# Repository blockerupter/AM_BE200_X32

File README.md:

AM_BE200_X32
============

BE200 Board with 32 chips

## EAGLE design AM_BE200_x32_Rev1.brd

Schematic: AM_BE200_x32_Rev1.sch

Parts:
C1, C17, C33, C49, C65, C81, C97, C113: 100uF; 153CLV-0605
C2, C3, C4, C5, C18, C19, C20, C21, C34, C35, C36, C37, C50, C51, C52, C53, C66, C67, C68, C69, C82, C83, C84, C85, C98, C99, C100, C101, C114, C115, C116, C117: 22uF; C1210K
C6, C7, C22, C23, C38, C39, C54, C55, C70, C71, C86, C87, C102, C103, C118, C119: 4.7uF; C0805K
C8, C24, C40, C56, C72, C88, C104, C120: 1nF; C0805K
C9, C25, C41, C57, C73, C89, C105, C121: 22nF; C0805K
C10, C26, C42, C58, C74, C90, C106, C122, C361, C362, C364, C367, C368, C369, C370, C371, C372: 100nF; C0805K
C11, C27, C43, C59, C75, C91, C107, C123, C354: 2,2nF; C0805K
C12, C13, C14, C15, C16, C28, C29, C30, C31, C32, C44, C45, C46, C47, C48, C60, C61, C62, C63, C64, C76, C77, C78, C79, C80, C92, C93, C94, C95, C96, C108, C109, C110, C111, C112, C124, C125, C126, C127, C128: 100uF; C1210K
C129, C130, C131, C132, C134, C136, C137, C138, C139, C141, C143, C144, C145, C146, C148, C150, C151, C152, C153, C155, C157, C158, C159, C160, C162, C164, C165, C166, C167, C169, C171, C172, C173, C174, C176, C178, C179, C180, C181, C183, C185, C186, C187, C188, C190, C192, C193, C194, C195, C197, C199, C200, C201, C202, C204, C206, C207, C208, C209, C211, C213, C214, C215, C216, C218, C220, C221, C222, C223, C225, C227, C228, C229, C230, C232, C234, C235, C236, C237, C239, C241, C242, C243, C244, C246, C248, C249, C250, C251, C253, C255, C256, C257, C258, C260, C262, C263, C264, C265, C267, C269, C270, C271, C272, C274, C276, C277, C278, C279, C281, C283, C284, C285, C286, C288, C290, C291, C292, C293, C295, C297, C298, C299, C300, C302, C304, C305, C306, C307, C309, C311, C312, C313, C314, C316, C318, C319, C320, C321, C323, C325, C326, C327, C328, C330, C332, C333, C334, C335, C337, C339, C340, C341, C342, C344, C346, C347, C348, C349, C351: 100nF; MYRCL_C0603K
C133, C135, C140, C142, C147, C149, C154, C156, C161, C163, C168, C170, C175, C177, C182, C184, C189, C191, C196, C198, C203, C205, C210, C212, C217, C219, C224, C226, C231, C233, C238, C240, C245, C247, C252, C254, C259, C261, C266, C268, C273, C275, C280, C282, C287, C289, C294, C296, C301, C303, C308, C310, C315, C317, C322, C324, C329, C331, C336, C338, C343, C345, C350, C352: 4.7uF; MYRCL_C0603K
C353: 10uF; C1206K
C355, C356: 22uF; C1206K
C357, C358, C359, C360, C363: 4,7uF; C0805K
C365, C366: 22pF; C0805K
D1: MBR_12V; SMBJ
IC1, IC2, IC3, IC4, IC5, IC6, IC7, IC8: TPS53353_TPS53355_DQP_22; DQP22_5P479X3P24
IC9, IC10, IC11, IC12, IC13, IC14, IC15, IC16, IC17, IC18, IC19, IC20, IC21, IC22, IC23, IC24, IC25, IC26, IC27, IC28, IC29, IC30, IC31, IC32, IC33, IC34, IC35, IC36, IC37, IC38, IC39, IC40: BE200_QFN64_9X9; QFN64-9X9
IC41: AOZ1021
IC42: TLV71209DBV; SOT-23-5
IC43: TLV7; SOT-23-5
IC44: MEGA88-AU; TQFP32-08
IC45, IC46, IC47, IC48, IC49: 74HC138D; SO16
IC50: 7407D; SO14
L1, L2, L3, L4, L5, L6, L7, L8: 0.47uH; INDUCTOR_PA0513
L9: 4.7uH; INDCUCTOR_7.3X7.3
Q1: 20MHZ; OSCILLATOR_7X5_SMD
Q2: 7.37MHZ; HC49UP
R1, R9, R17, R25, R33, R41, R49, R57: 39K; R0805K
R2, R10, R18, R26, R34, R42, R50, R58: 180K; R0805K
R3, R11, R19, R27, R35, R43, R51, R59: 200K; R0805K
R4, R12, R20, R28, R36, R44, R52, R60: 100K; R0805K
R5, R13, R21, R29, R37, R45, R53, R61: 10K; R0805K
R6, R14, R22, R30, R38, R46, R54, R62: 5K; S64W
R6A, R14A, R22A, R30A, R38A, R46A, R54A, R62A: 2K49; R0805K
R7, R15, R23, R31, R39, R47, R55, R63: 56K; R0805K
R8, R16, R24, R32, R40, R48, R56, R64: 3 or 3.01; R0805K
R65, R66, R67: 7K5; R0805K
R68: 2K4; R0805K
R69, R70: 4K7; R0805K
S1: 219-05; CTS-219-05
X1, X2: MINI-FIT-JR-065.5MM; PCIE6_4.2
X3: 22-23-2031
X4, X5: XH2.54-3P
X6: AVR-ISP-6VERT; AVR-ISP-6

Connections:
0.9V: C130.1, C137.1, C144.1, C151.1, C158.1, C165.1, C172.1, C179.1, C186.1, C193.1, C200.1, C207.1, C214.1, C221.1, C228.1, C235.1, C242.1, C249.1, C256.1, C263.1, C270.1, C277.1, C284.1, C291.1, C298.1, C305.1, C312.1, C319.1, C326.1, C333.1, C340.1, C347.1, C358.2, IC9.8 (PLLDVDD), IC9.10 (PLLVDD), IC10.8 (PLLDVDD), IC10.10 (PLLVDD), IC11.8 (PLLDVDD), IC11.10 (PLLVDD), IC12.8 (PLLDVDD), IC12.10 (PLLVDD), IC13.8 (PLLDVDD), IC13.10 (PLLVDD), IC14.8 (PLLDVDD), IC14.10 (PLLVDD), IC15.8 (PLLDVDD), IC15.10 (PLLVDD), IC16.8 (PLLDVDD), IC16.10 (PLLVDD), IC17.8 (PLLDVDD), IC17.10 (PLLVDD), IC18.8 (PLLDVDD), IC18.10 (PLLVDD), IC19.8 (PLLDVDD), IC19.10 (PLLVDD), IC20.8 (PLLDVDD), IC20.10 (PLLVDD), IC21.8 (PLLDVDD), IC21.10 (PLLVDD), IC22.8 (PLLDVDD), IC22.10 (PLLVDD), IC23.8 (PLLDVDD), IC23.10 (PLLVDD), IC24.8 (PLLDVDD), IC24.10 (PLLVDD), IC25.8 (PLLDVDD), IC25.10 (PLLVDD), IC26.8 (PLLDVDD), IC26.10 (PLLVDD), IC27.8 (PLLDVDD), IC27.10 (PLLVDD), IC28.8 (PLLDVDD), IC28.10 (PLLVDD), IC29.8 (PLLDVDD), IC29.10 (PLLVDD), IC30.8 (PLLDVDD), IC30.10 (PLLVDD), IC31.8 (PLLDVDD), IC31.10 (PLLVDD), IC32.8 (PLLDVDD), IC32.10 (PLLVDD), IC33.8 (PLLDVDD), IC33.10 (PLLVDD), IC34.8 (PLLDVDD), IC34.10 (PLLVDD), IC35.8 (PLLDVDD), IC35.10 (PLLVDD), IC36.8 (PLLDVDD), IC36.10 (PLLVDD), IC37.8 (PLLDVDD), IC37.10 (PLLVDD), IC38.8 (PLLDVDD), IC38.10 (PLLVDD), IC39.8 (PLLDVDD), IC39.10 (PLLVDD), IC40.8 (PLLDVDD), IC40.10 (PLLVDD), IC42.5 (OUT)
1.8V: C129.2, C131.1, C136.2, C138.1, C143.2, C145.1, C150.2, C152.1, C157.2, C159.1, C164.2, C166.1, C171.2, C173.1, C178.2, C180.1, C185.2, C187.1, C192.2, C194.1, C199.2, C201.1, C206.2, C208.1, C213.2, C215.1, C220.2, C222.1, C227.2, C229.1, C234.2, C236.1, C241.2, C243.1, C248.2, C250.1, C255.2, C257.1, C262.2, C264.1, C269.2, C271.1, C276.2, C278.1, C283.2, C285.1, C290.2, C292.1, C297.2, C299.1, C304.2, C306.1, C311.2, C313.1, C318.2, C320.1, C325.2, C327.1, C332.2, C334.1, C339.2, C341.1, C346.2, C348.1, C360.2, IC9.5 (PLLIOVDD), IC9.6 (PLLAHVDD), IC9.25 (VDD_IO), IC9.37 (VDD_IO), IC9.56 (VDD_IO), IC10.5 (PLLIOVDD), IC10.6 (PLLAHVDD), IC10.25 (VDD_IO), IC10.37 (VDD_IO), IC10.56 (VDD_IO), IC11.5 (PLLIOVDD), IC11.6 (PLLAHVDD), IC11.25 (VDD_IO), IC11.37 (VDD_IO), IC11.56 (VDD_IO), IC12.5 (PLLIOVDD), IC12.6 (PLLAHVDD), IC12.25 (VDD_IO), IC12.37 (VDD_IO), IC12.56 (VDD_IO), IC13.5 (PLLIOVDD), IC13.6 (PLLAHVDD), IC13.25 (VDD_IO), IC13.37 (VDD_IO), IC13.56 (VDD_IO), IC14.5 (PLLIOVDD), IC14.6 (PLLAHVDD), IC14.25 (VDD_IO), IC14.37 (VDD_IO), IC14.56 (VDD_IO), IC15.5 (PLLIOVDD), IC15.6 (PLLAHVDD), IC15.25 (VDD_IO), IC15.37 (VDD_IO), IC15.56 (VDD_IO), IC16.5 (PLLIOVDD), IC16.6 (PLLAHVDD), IC16.25 (VDD_IO), IC16.37 (VDD_IO), IC16.56 (VDD_IO), IC17.5 (PLLIOVDD), IC17.6 (PLLAHVDD), IC17.25 (VDD_IO), IC17.37 (VDD_IO), IC17.56 (VDD_IO), IC18.5 (PLLIOVDD), IC18.6 (PLLAHVDD), IC18.25 (VDD_IO), IC18.37 (VDD_IO), IC18.56 (VDD_IO), IC19.5 (PLLIOVDD), IC19.6 (PLLAHVDD), IC19.25 (VDD_IO), IC19.37 (VDD_IO), IC19.56 (VDD_IO), IC20.5 (PLLIOVDD), IC20.6 (PLLAHVDD), IC20.25 (VDD_IO), IC20.37 (VDD_IO), IC20.56 (VDD_IO), IC21.5 (PLLIOVDD), IC21.6 (PLLAHVDD), IC21.25 (VDD_IO), IC21.37 (VDD_IO), IC21.56 (VDD_IO), IC22.5 (PLLIOVDD), IC22.6 (PLLAHVDD), IC22.25 (VDD_IO), IC22.37 (VDD_IO), IC22.56 (VDD_IO), IC23.5 (PLLIOVDD), IC23.6 (PLLAHVDD), IC23.25 (VDD_IO), IC23.37 (VDD_IO), IC23.56 (VDD_IO), IC24.5 (PLLIOVDD), IC24.6 (PLLAHVDD), IC24.25 (VDD_IO), IC24.37 (VDD_IO)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
+3V3: C355.1, C356.1, C357.2, C359.2, C361.2, C362.2, C363.2, C367.2, C368.2, C369.2, C370.2, C371.2, C372.2, IC42.1 (IN), IC42.3 (EN), IC43.1 (IN), IC43.3 (EN), IC44.4 (VCC), IC44.6 (VCC), IC44.18 (AVCC), IC45.16 (VCC), IC46.6 (G1), IC46.16 (VCC), IC47.6 (G1), IC47.16 (VCC), IC48.6 (G1), IC48.16 (VCC), IC49.6 (G1), IC49.16 (VCC), IC50.14 (VCC), L9.2, Q1.1 (EN), Q1.4 (VCC), R67.2, R69.2, R70.2, X6.2
+12V: C1.+, C2.1, C3.1, C4.1, C5.1, C7.1, C17.+, C18.1, C19.1, C20.1, C21.1, C23.1, C33.+, C34.1, C35.1, C36.1, C37.1, C39.1, C49.+, C50.1, C51.1, C52.1, C53.1, C55.1, C65.+, C66.1, C67.1, C68.1, C69.1, C71.1, C81.+, C82.1, C83.1, C84.1, C85.1, C87.1, C97.+, C98.1, C99.1, C100.1, C101.1, C103.1, C113.+, C114.1, C115.1, C116.1, C117.1, C119.1, C353.1, D1.C, IC1.12 (VIN_2), IC1.13 (VIN_3), IC1.14 (VIN_4), IC1.15 (VIN_5), IC1.16 (VIN_6), IC1.17 (VIN), IC1.19 (VDD), IC2.12 (VIN_2), IC2.13 (VIN_3), IC2.14 (VIN_4), IC2.15 (VIN_5), IC2.16 (VIN_6), IC2.17 (VIN), IC2.19 (VDD), IC3.12 (VIN_2), IC3.13 (VIN_3), IC3.14 (VIN_4), IC3.15 (VIN_5), IC3.16 (VIN_6), IC3.17 (VIN), IC3.19 (VDD), IC4.12 (VIN_2), IC4.13 (VIN_3), IC4.14 (VIN_4), IC4.15 (VIN_5), IC4.16 (VIN_6), IC4.17 (VIN), IC4.19 (VDD), IC5.12 (VIN_2), IC5.13 (VIN_3), IC5.14 (VIN_4), IC5.15 (VIN_5), IC5.16 (VIN_6), IC5.17 (VIN), IC5.19 (VDD), IC6.12 (VIN_2), IC6.13 (VIN_3), IC6.14 (VIN_4), IC6.15 (VIN_5), IC6.16 (VIN_6), IC6.17 (VIN), IC6.19 (VDD), IC7.12 (VIN_2), IC7.13 (VIN_3), IC7.14 (VIN_4), IC7.15 (VIN_5), IC7.16 (VIN_6), IC7.17 (VIN), IC7.19 (VDD), IC8.12 (VIN_2), IC8.13 (VIN_3), IC8.14 (VIN_4), IC8.15 (VIN_5), IC8.16 (VIN_6), IC8.17 (VIN), IC8.19 (VDD), IC41.VIN, R3.2, R11.2, R19.2, R27.2, R35.2, R43.2, R51.2, R59.2, R65.2, X1.P1 (1), X1.P2 (2), X1.P3 (3), X2.P1 (1), X2.P2 (2), X2.P3 (3), X3.2
/CS_EN: IC44.14 (PB2(SS/OC1B/PCINT2)), IC45.4 (G2A), IC45.5 (G2B), R70.1
A0: IC44.23 (PC0(ADC0/PCINT8)), IC46.1 (A), IC47.1 (A), IC48.1 (A), IC49.1 (A)
A1: IC44.24 (PC1(ADC1/PCINT9)), IC46.2 (B), IC47.2 (B), IC48.2 (B), IC49.2 (B)
A2: IC44.25 (PC2(ADC2/PCINT10)), IC46.3 (C), IC47.3 (C), IC48.3 (C), IC49.3 (C)
A3: IC44.26 (PC3(ADC3/PCINT11)), IC45.1 (A)
A4: IC44.27 (PC4(ADC4/SDA/PCINT12)), IC45.2 (B)
BID0: IC44.32 (PD2(INT0/PCINT18)), S1.5
BID1: IC44.1 (PD3(INT1/OC2B/PCINT19)), S1.4
BID2: IC44.2 (PD4(T0/XCK/PCINT20)), S1.3
BID3: IC44.9 (PD5(T1/OC0B/PCINT21)), S1.2
BID4: IC44.10 (PD6(AIN0/OC0A/PCINT22)), S1.1
BS: IC9.13 (BS), IC10.13 (BS), IC11.13 (BS), IC12.13 (BS), IC13.13 (BS), IC14.13 (BS), IC15.13 (BS), IC16.13 (BS), IC17.13 (BS), IC18.13 (BS), IC19.13 (BS), IC20.13 (BS), IC21.13 (BS), IC22.13 (BS), IC23.13 (BS), IC24.13 (BS), IC25.13 (BS), IC26.13 (BS), IC27.13 (BS), IC28.13 (BS), IC29.13 (BS), IC30.13 (BS), IC31.13 (BS), IC32.13 (BS), IC33.13 (BS), IC34.13 (BS), IC35.13 (BS), IC36.13 (BS), IC37.13 (BS), IC38.13 (BS), IC39.13 (BS), IC40.13 (BS), IC44.11 (PD7(AIN1/PCINT23))
CE0: IC45.15 (Y0), IC46.4 (G2A), IC46.5 (G2B)
CE1: IC45.14 (Y1), IC47.4 (G2A), IC47.5 (G2B)
CE2: IC45.13 (Y2), IC48.4 (G2A), IC48.5 (G2B)
CE3: IC45.12 (Y3), IC49.4 (G2A), IC49.5 (G2B)
CS0: IC9.39 (/CS_(SS)), IC46.15 (Y0)
CS1: IC10.39 (/CS_(SS)), IC46.14 (Y1)
CS2: IC11.39 (/CS_(SS)), IC46.13 (Y2)
CS3: IC12.39 (/CS_(SS)), IC46.12 (Y3)
CS4: IC13.39 (/CS_(SS)), IC46.11 (Y4)
CS5: IC14.39 (/CS_(SS)), IC46.10 (Y5)
CS6: IC15.39 (/CS_(SS)), IC46.9 (Y6)
CS7: IC16.39 (/CS_(SS)), IC46.7 (Y7)
CS8: IC17.39 (/CS_(SS)), IC47.15 (Y0)
CS9: IC18.39 (/CS_(SS)), IC47.14 (Y1)
CS10: IC19.39 (/CS_(SS)), IC47.13 (Y2)
CS11: IC20.39 (/CS_(SS)), IC47.12 (Y3)
CS12: IC21.39 (/CS_(SS)), IC47.11 (Y4)
CS13: IC22.39 (/CS_(SS)), IC47.10 (Y5)
CS14: IC23.39 (/CS_(SS)), IC47.9 (Y6)
CS15: IC24.39 (/CS_(SS)), IC47.7 (Y7)
CS16: IC25.39 (/CS_(SS)), IC48.15 (Y0)
CS17: IC26.39 (/CS_(SS)), IC48.14 (Y1)
CS18: IC27.39 (/CS_(SS)), IC48.13 (Y2)
CS19: IC28.39 (/CS_(SS)), IC48.12 (Y3)
CS20: IC29.39 (/CS_(SS)), IC48.11 (Y4)
CS21: IC30.39 (/CS_(SS)), IC48.10 (Y5)
CS22: IC31.39 (/CS_(SS)), IC48.9 (Y6)
CS23: IC32.39 (/CS_(SS)), IC48.7 (Y7)
CS24: IC33.39 (/CS_(SS)), IC49.15 (Y0)
CS25: IC34.39 (/CS_(SS)), IC49.14 (Y1)
CS26: IC35.39 (/CS_(SS)), IC49.13 (Y2)
CS27: IC36.39 (/CS_(SS)), IC49.12 (Y3)
CS28: IC37.39 (/CS_(SS)), IC49.11 (Y4)
CS29: IC38.39 (/CS_(SS)), IC49.10 (Y5)
CS30: IC39.39 (/CS_(SS)), IC49.9 (Y6)
CS31: IC40.39 (/CS_(SS)), IC49.7 (Y7)
EN_SITE1: IC1.2 (EN), R3.1, R4.2
EN_SITE2: IC2.2 (EN), R11.1, R12.2
EN_SITE3: IC3.2 (EN), R19.1, R20.2
EN_SITE4: IC4.2 (EN), R27.1, R28.2
EN_SITE5: IC5.2 (EN), R35.1, R36.2
EN_SITE6: IC6.2 (EN), R43.1, R44.2
EN_SITE7: IC7.2 (EN), R51.1, R52.2
EN_SITE8: IC8.2 (EN), R59.1, R60.2
GND: C1.-, C2.2, C3.2, C4.2, C5.2, C6.2, C7.2, C11.2, C12.2, C13.2, C14.2, C15.2, C16.2, C17.-, C18.2, C19.2, C20.2, C21.2, C22.2, C23.2, C27.2, C28.2, C29.2, C30.2, C31.2, C32.2, C33.-, C34.2, C35.2, C36.2, C37.2, C38.2, C39.2, C43.2, C44.2, C45.2, C46.2, C47.2, C48.2, C49.-, C50.2, C51.2, C52.2, C53.2, C54.2, C55.2, C59.2, C60.2, C61.2, C62.2, C63.2, C64.2, C65.-, C66.2, C67.2, C68.2, C69.2, C70.2, C71.2, C75.2, C76.2, C77.2, C78.2, C79.2, C80.2, C81.-, C82.2, C83.2, C84.2, C85.2, C86.2, C87.2, C91.2, C92.2, C93.2, C94.2, C95.2, C96.2, C97.-, C98.2, C99.2, C100.2, C101.2, C102.2, C103.2, C107.2, C108.2, C109.2, C110.2, C111.2, C112.2, C113.-, C114.2, C115.2, C116.2, C117.2, C118.2, C119.2, C123.2, C124.2, C125.2, C126.2, C127.2, C128.2, C129.1, C130.2, C131.2, C132.2, C133.2, C134.2, C135.2, C136.1, C137.2, C138.2, C139.2, C140.2, C141.2, C142.2, C143.1, C144.2, C145.2, C146.2, C147.2, C148.2, C149.2, C150.1, C151.2, C152.2, C153.2, C154.2, C155.2, C156.2, C157.1, C158.2, C159.2, C160.2, C161.2, C162.2, C163.2, C164.1, C165.2, C166.2, C167.2, C168.2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
HARD0: IC9.43 (HARD0), IC10.43 (HARD0), IC11.43 (HARD0), IC12.43 (HARD0), IC13.43 (HARD0), IC14.43 (HARD0), IC15.43 (HARD0), IC16.43 (HARD0), IC17.43 (HARD0), IC18.43 (HARD0), IC19.43 (HARD0), IC20.43 (HARD0), IC21.43 (HARD0), IC22.43 (HARD0), IC23.43 (HARD0), IC24.43 (HARD0), IC25.43 (HARD0), IC26.43 (HARD0), IC27.43 (HARD0), IC28.43 (HARD0), IC29.43 (HARD0), IC30.43 (HARD0), IC31.43 (HARD0), IC32.43 (HARD0), IC33.43 (HARD0), IC34.43 (HARD0), IC35.43 (HARD0), IC36.43 (HARD0), IC37.43 (HARD0), IC38.43 (HARD0), IC39.43 (HARD0), IC40.43 (HARD0), IC44.12 (PB0(ICP1/CLKO/PCINT0))
HARD1: IC9.44 (HARD1), IC10.44 (HARD1), IC11.44 (HARD1), IC12.44 (HARD1), IC13.44 (HARD1), IC14.44 (HARD1), IC15.44 (HARD1), IC16.44 (HARD1), IC17.44 (HARD1), IC18.44 (HARD1), IC19.44 (HARD1), IC20.44 (HARD1), IC21.44 (HARD1), IC22.44 (HARD1), IC23.44 (HARD1), IC24.44 (HARD1), IC25.44 (HARD1), IC26.44 (HARD1), IC27.44 (HARD1), IC28.44 (HARD1), IC29.44 (HARD1), IC30.44 (HARD1), IC31.44 (HARD1), IC32.44 (HARD1), IC33.44 (HARD1), IC34.44 (HARD1), IC35.44 (HARD1), IC36.44 (HARD1), IC37.44 (HARD1), IC38.44 (HARD1), IC39.44 (HARD1), IC40.44 (HARD1), IC44.13 (PB1(OC1A/PCINT1))
MCU_RESET: IC44.29 (PC6(/RESET/PCINT14)), IC45.6 (G1), R69.1, X6.5
MISO_3.3V: IC9.41 (SO), IC10.41 (SO), IC11.41 (SO), IC12.41 (SO), IC13.41 (SO), IC14.41 (SO), IC15.41 (SO), IC16.41 (SO), IC17.41 (SO), IC18.41 (SO), IC19.41 (SO), IC20.41 (SO), IC21.41 (SO), IC22.41 (SO), IC23.41 (SO), IC24.41 (SO), IC25.41 (SO), IC26.41 (SO), IC27.41 (SO), IC28.41 (SO), IC29.41 (SO), IC30.41 (SO), IC31.41 (SO), IC32.41 (SO), IC33.41 (SO), IC34.41 (SO), IC35.41 (SO), IC36.41 (SO), IC37.41 (SO), IC38.41 (SO), IC39.41 (SO), IC40.41 (SO), IC44.16 (PB4(MISO/PCINT4)), X6.1
MOSI_3.3V: IC9.42 (SI), IC10.42 (SI), IC11.42 (SI), IC12.42 (SI), IC13.42 (SI), IC14.42 (SI), IC15.42 (SI), IC16.42 (SI), IC17.42 (SI), IC18.42 (SI), IC19.42 (SI), IC20.42 (SI), IC21.42 (SI), IC22.42 (SI), IC23.42 (SI), IC24.42 (SI), IC25.42 (SI), IC26.42 (SI), IC27.42 (SI), IC28.42 (SI), IC29.42 (SI), IC30.42 (SI), IC31.42 (SI), IC32.42 (SI), IC33.42 (SI), IC34.42 (SI), IC35.42 (SI), IC36.42 (SI), IC37.42 (SI), IC38.42 (SI), IC39.42 (SI), IC40.42 (SI), IC44.15 (PB3(MOSI/OC2A/PCINT3)), X6.4
unnamed: C10.2, IC1.6 (LL_2), IC1.7 (LL_3), IC1.8 (LL_4), IC1.9 (LL_5), IC1.10 (LL_6), IC1.11 (LL), L1.2, R7.2, R8.2
unnamed: C11.1, R8.1
unnamed: C8.1, C9.2, R7.1
unnamed: IC1.21 (TRIP), R2.2
unnamed: IC1.20 (MODE), R1.2
unnamed: C6.1, IC1.18 (VREG)
unnamed: C26.2, IC2.6 (LL_2), IC2.7 (LL_3), IC2.8 (LL_4), IC2.9 (LL_5), IC2.10 (LL_6), IC2.11 (LL), L2.2, R15.2, R16.2
unnamed: IC2.21 (TRIP), R10.2
unnamed: C10.1, IC1.4 (VBST)
unnamed: IC2.20 (MODE), R9.2
unnamed: C22.1, IC2.18 (VREG)
unnamed: C26.1, IC2.4 (VBST)
unnamed: C354.1, R66.1
unnamed: C27.1, R16.1
unnamed: C24.1, C25.2, R15.1
unnamed: IC41.LX, L9.1
unnamed: C42.2, IC3.6 (LL_2), IC3.7 (LL_3), IC3.8 (LL_4), IC3.9 (LL_5), IC3.10 (LL_6), IC3.11 (LL), L3.2, R23.2, R24.2
unnamed: IC41.FB, R67.1, R68.2
unnamed: IC41.COMP, R66.2
unnamed: IC41.EN, R65.1
unnamed: C364.2, IC44.20 (AREF)
unnamed: IC3.21 (TRIP), R18.2
unnamed: IC3.20 (MODE), R17.2
unnamed: C38.1, IC3.18 (VREG)
unnamed: C366.1, IC44.7 (PB6(XTAL1/TOSC1/PCINT6)), Q2.2
unnamed: C42.1, IC3.4 (VBST)
unnamed: C43.1, R24.1
unnamed: C365.1, IC44.8 (PB7(XTAL2/TOSC2/PCINT7)), Q2.1
unnamed: C40.1, C41.2, R23.1
unnamed: C58.2, IC4.6 (LL_2), IC4.7 (LL_3), IC4.8 (LL_4), IC4.9 (LL_5), IC4.10 (LL_6), IC4.11 (LL), L4.2, R31.2, R32.2
unnamed: IC4.21 (TRIP), R26.2
unnamed: IC4.20 (MODE), R25.2
unnamed: C54.1, IC4.18 (VREG)
unnamed: C58.1, IC4.4 (VBST)
unnamed: C59.1, R32.1
unnamed: C56.1, C57.2, R31.1
unnamed: C74.2, IC5.6 (LL_2), IC5.7 (LL_3), IC5.8 (LL_4), IC5.9 (LL_5), IC5.10 (LL_6), IC5.11 (LL), L5.2, R39.2, R40.2
unnamed: IC5.21 (TRIP), R34.2
unnamed: IC5.20 (MODE), R33.2
unnamed: C70.1, IC5.18 (VREG)
unnamed: C74.1, IC5.4 (VBST)
unnamed: C75.1, R40.1
unnamed: C72.1, C73.2, R39.1
unnamed: C90.2, IC6.6 (LL_2), IC6.7 (LL_3), IC6.8 (LL_4), IC6.9 (LL_5), IC6.10 (LL_6), IC6.11 (LL), L6.2, R47.2, R48.2
unnamed: IC6.21 (TRIP), R42.2
unnamed: IC6.20 (MODE), R41.2
unnamed: C86.1, IC6.18 (VREG)
unnamed: C90.1, IC6.4 (VBST)
unnamed: C91.1, R48.1
unnamed: C88.1, C89.2, R47.1
unnamed: C106.2, IC7.6 (LL_2), IC7.7 (LL_3), IC7.8 (LL_4), IC7.9 (LL_5), IC7.10 (LL_6), IC7.11 (LL), L7.2, R55.2, R56.2
unnamed: IC7.21 (TRIP), R50.2
unnamed: IC7.20 (MODE), R49.2
unnamed: C102.1, IC7.18 (VREG)
unnamed: C106.1, IC7.4 (VBST)
unnamed: C107.1, R56.1
unnamed: C104.1, C105.2, R55.1
unnamed: C122.2, IC8.6 (LL_2), IC8.7 (LL_3), IC8.8 (LL_4), IC8.9 (LL_5), IC8.10 (LL_6), IC8.11 (LL), L8.2, R63.2, R64.2
unnamed: IC8.21 (TRIP), R58.2
unnamed: IC8.20 (MODE), R57.2
unnamed: C118.1, IC8.18 (VREG)
unnamed: C122.1, IC8.4 (VBST)
unnamed: C123.1, R64.1
unnamed: C120.1, C121.2, R63.1
OSC_CLK: IC9.12 (OSC_CLK), IC10.12 (OSC_CLK), IC11.12 (OSC_CLK), IC12.12 (OSC_CLK), IC13.12 (OSC_CLK), IC14.12 (OSC_CLK), IC15.12 (OSC_CLK), IC16.12 (OSC_CLK), IC17.12 (OSC_CLK), IC18.12 (OSC_CLK), IC19.12 (OSC_CLK), IC20.12 (OSC_CLK), IC21.12 (OSC_CLK), IC22.12 (OSC_CLK), IC23.12 (OSC_CLK), IC24.12 (OSC_CLK), IC25.12 (OSC_CLK), IC26.12 (OSC_CLK), IC27.12 (OSC_CLK), IC28.12 (OSC_CLK), IC29.12 (OSC_CLK), IC30.12 (OSC_CLK), IC31.12 (OSC_CLK), IC32.12 (OSC_CLK), IC33.12 (OSC_CLK), IC34.12 (OSC_CLK), IC35.12 (OSC_CLK), IC36.12 (OSC_CLK), IC37.12 (OSC_CLK), IC38.12 (OSC_CLK), IC39.12 (OSC_CLK), IC40.12 (OSC_CLK), Q1.3 (OUT)
RESET: IC9.38 (RESET), IC10.38 (RESET), IC11.38 (RESET), IC12.38 (RESET), IC13.38 (RESET), IC14.38 (RESET), IC15.38 (RESET), IC16.38 (RESET), IC17.38 (RESET), IC18.38 (RESET), IC19.38 (RESET), IC20.38 (RESET), IC21.38 (RESET), IC22.38 (RESET), IC23.38 (RESET), IC24.38 (RESET), IC25.38 (RESET), IC26.38 (RESET), IC27.38 (RESET), IC28.38 (RESET), IC29.38 (RESET), IC30.38 (RESET), IC31.38 (RESET), IC32.38 (RESET), IC33.38 (RESET), IC34.38 (RESET), IC35.38 (RESET), IC36.38 (RESET), IC37.38 (RESET), IC38.38 (RESET), IC39.38 (RESET), IC40.38 (RESET), IC44.28 (PC5(ADC5/SCL/PCINT13))
RXD: IC44.30 (PD0(RXD/PCINT16)), X4.1, X5.1
SCK_3.3V: IC9.40 (SCK), IC10.40 (SCK), IC11.40 (SCK), IC12.40 (SCK), IC13.40 (SCK), IC14.40 (SCK), IC15.40 (SCK), IC16.40 (SCK), IC17.40 (SCK), IC18.40 (SCK), IC19.40 (SCK), IC20.40 (SCK), IC21.40 (SCK), IC22.40 (SCK), IC23.40 (SCK), IC24.40 (SCK), IC25.40 (SCK), IC26.40 (SCK), IC27.40 (SCK), IC28.40 (SCK), IC29.40 (SCK), IC30.40 (SCK), IC31.40 (SCK), IC32.40 (SCK), IC33.40 (SCK), IC34.40 (SCK), IC35.40 (SCK), IC36.40 (SCK), IC37.40 (SCK), IC38.40 (SCK), IC39.40 (SCK), IC40.40 (SCK), IC44.17 (PB5(SCK/PCINT5)), X6.3
TXD: IC50.2 (O), IC50.4 (O), IC50.6 (O), IC50.8 (O), IC50.10 (O), IC50.12 (O), X4.2, X5.2
TXD_MCU: IC44.31 (PD1(TXD/PCINT17)), IC50.1 (I), IC50.3 (I), IC50.5 (I), IC50.9 (I), IC50.11 (I), IC50.13 (I)
VCORE_SITE1: C9.1, C12.1, C13.1, C14.1, C15.1, C16.1, C132.1, C133.1, C134.1, C135.1, C139.1, C140.1, C141.1, C142.1, C146.1, C147.1, C148.1, C149.1, C153.1, C154.1, C155.1, C156.1, IC9.1 (VDD_CORE), IC9.2 (VDD_CORE), IC9.3 (VDD_CORE), IC9.4 (VDD_CORE), IC9.14 (VDD_CORE), IC9.15 (VDD_CORE), IC9.16 (VDD_CORE), IC9.17 (VDD_CORE), IC9.18 (VDD_CORE), IC9.19 (VDD_CORE), IC9.20 (VDD_CORE), IC9.21 (VDD_CORE), IC9.22 (VDD_CORE), IC9.23 (VDD_CORE), IC9.24 (VDD_CORE), IC9.26 (VDD_CORE), IC9.27 (VDD_CORE), IC9.28 (VDD_CORE), IC9.29 (VDD_CORE), IC9.30 (VDD_CORE), IC9.31 (VDD_CORE), IC9.32 (VDD_CORE), IC9.33 (VDD_CORE), IC9.34 (VDD_CORE), IC9.35 (VDD_CORE), IC9.36 (VDD_CORE), IC9.45 (VDD_CORE), IC9.46 (VDD_CORE), IC9.47 (VDD_CORE), IC9.48 (VDD_CORE), IC9.49 (VDD_CORE), IC9.50 (VDD_CORE), IC9.51 (VDD_CORE), IC9.52 (VDD_CORE), IC9.53 (VDD_CORE), IC9.54 (VDD_CORE), IC9.55 (VDD_CORE), IC9.57 (VDD_CORE), IC9.58 (VDD_CORE), IC9.59 (VDD_CORE), IC9.60 (VDD_CORE), IC9.61 (VDD_CORE), IC9.62 (VDD_CORE), IC9.63 (VDD_CORE), IC9.64 (VDD_CORE), IC10.1 (VDD_CORE), IC10.2 (VDD_CORE), IC10.3 (VDD_CORE), IC10.4 (VDD_CORE), IC10.14 (VDD_CORE), IC10.15 (VDD_CORE), IC10.16 (VDD_CORE), IC10.17 (VDD_CORE), IC10.18 (VDD_CORE), IC10.19 (VDD_CORE), IC10.20 (VDD_CORE), IC10.21 (VDD_CORE), IC10.22 (VDD_CORE), IC10.23 (VDD_CORE), IC10.24 (VDD_CORE), IC10.26 (VDD_CORE), IC10.27 (VDD_CORE), IC10.28 (VDD_CORE), IC10.29 (VDD_CORE), IC10.30 (VDD_CORE), IC10.31 (VDD_CORE), IC10.32 (VDD_CORE), IC10.33 (VDD_CORE), IC10.34 (VDD_CORE), IC10.35 (VDD_CORE), IC10.36 (VDD_CORE), IC10.45 (VDD_CORE), IC10.46 (VDD_CORE), IC10.47 (VDD_CORE), IC10.48 (VDD_CORE), IC10.49 (VDD_CORE), IC10.50 (VDD_CORE), IC10.51 (VDD_CORE), IC10.52 (VDD_CORE), IC10.53 (VDD_CORE), IC10.54 (VDD_CORE), IC10.55 (VDD_CORE), IC10.57 (VDD_CORE), IC10.58 (VDD_CORE), IC10.59 (VDD_CORE), IC10.60 (VDD_CORE), IC10.61 (VDD_CORE), IC10.62 (VDD_CORE), IC10.63 (VDD_CORE), IC10.64 (VDD_CORE), IC11.1 (VDD_CORE), IC11.2 (VDD_CORE), IC11.3 (VDD_CORE), IC11.4 (VDD_CORE), IC11.14 (VDD_CORE), IC11.15 (VDD_CORE), IC11.16 (VDD_CORE), IC11.17 (VDD_CORE), IC11.18 (VDD_CORE), IC11.19 (VDD_CORE), IC11.20 (VDD_CORE), IC11.21 (VDD_CORE), IC11.22 (VDD_CORE), IC11.23 (VDD_CORE), IC11.24 (VDD_CORE), IC11.26 (VDD_CORE), IC11.27 (VDD_CORE), IC11.28 (VDD_CORE), IC11.29 (VDD_CORE), IC11.30 (VDD_CORE), IC11.31 (VDD_CORE), IC11.32 (VDD_CORE), IC11.33 (VDD_CORE), IC11.34 (VDD_CORE), IC11.35 (VDD_CORE), IC11.36 (VDD_CORE), IC11.45 (VDD_CORE), IC11.46 (VDD_CORE), IC11.47 (VDD_CORE), IC11.48 (VDD_CORE), IC11.49 (VDD_CORE), IC11.50 (VDD_CORE)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
VCORE_SITE2: C25.1, C28.1, C29.1, C30.1, C31.1, C32.1, C160.1, C161.1, C162.1, C163.1, C167.1, C168.1, C169.1, C170.1, C174.1, C175.1, C176.1, C177.1, C181.1, C182.1, C183.1, C184.1, IC13.1 (VDD_CORE), IC13.2 (VDD_CORE), IC13.3 (VDD_CORE), IC13.4 (VDD_CORE), IC13.14 (VDD_CORE), IC13.15 (VDD_CORE), IC13.16 (VDD_CORE), IC13.17 (VDD_CORE), IC13.18 (VDD_CORE), IC13.19 (VDD_CORE), IC13.20 (VDD_CORE), IC13.21 (VDD_CORE), IC13.22 (VDD_CORE), IC13.23 (VDD_CORE), IC13.24 (VDD_CORE), IC13.26 (VDD_CORE), IC13.27 (VDD_CORE), IC13.28 (VDD_CORE), IC13.29 (VDD_CORE), IC13.30 (VDD_CORE), IC13.31 (VDD_CORE), IC13.32 (VDD_CORE), IC13.33 (VDD_CORE), IC13.34 (VDD_CORE), IC13.35 (VDD_CORE), IC13.36 (VDD_CORE), IC13.45 (VDD_CORE), IC13.46 (VDD_CORE), IC13.47 (VDD_CORE), IC13.48 (VDD_CORE), IC13.49 (VDD_CORE), IC13.50 (VDD_CORE), IC13.51 (VDD_CORE), IC13.52 (VDD_CORE), IC13.53 (VDD_CORE), IC13.54 (VDD_CORE), IC13.55 (VDD_CORE), IC13.57 (VDD_CORE), IC13.58 (VDD_CORE), IC13.59 (VDD_CORE), IC13.60 (VDD_CORE), IC13.61 (VDD_CORE), IC13.62 (VDD_CORE), IC13.63 (VDD_CORE), IC13.64 (VDD_CORE), IC14.1 (VDD_CORE), IC14.2 (VDD_CORE), IC14.3 (VDD_CORE), IC14.4 (VDD_CORE), IC14.14 (VDD_CORE), IC14.15 (VDD_CORE), IC14.16 (VDD_CORE), IC14.17 (VDD_CORE), IC14.18 (VDD_CORE), IC14.19 (VDD_CORE), IC14.20 (VDD_CORE), IC14.21 (VDD_CORE), IC14.22 (VDD_CORE), IC14.23 (VDD_CORE), IC14.24 (VDD_CORE), IC14.26 (VDD_CORE), IC14.27 (VDD_CORE), IC14.28 (VDD_CORE), IC14.29 (VDD_CORE), IC14.30 (VDD_CORE), IC14.31 (VDD_CORE), IC14.32 (VDD_CORE), IC14.33 (VDD_CORE), IC14.34 (VDD_CORE), IC14.35 (VDD_CORE), IC14.36 (VDD_CORE), IC14.45 (VDD_CORE), IC14.46 (VDD_CORE), IC14.47 (VDD_CORE), IC14.48 (VDD_CORE), IC14.49 (VDD_CORE), IC14.50 (VDD_CORE), IC14.51 (VDD_CORE), IC14.52 (VDD_CORE), IC14.53 (VDD_CORE), IC14.54 (VDD_CORE), IC14.55 (VDD_CORE), IC14.57 (VDD_CORE), IC14.58 (VDD_CORE), IC14.59 (VDD_CORE), IC14.60 (VDD_CORE), IC14.61 (VDD_CORE), IC14.62 (VDD_CORE), IC14.63 (VDD_CORE), IC14.64 (VDD_CORE), IC15.1 (VDD_CORE), IC15.2 (VDD_CORE), IC15.3 (VDD_CORE), IC15.4 (VDD_CORE), IC15.14 (VDD_CORE), IC15.15 (VDD_CORE), IC15.16 (VDD_CORE), IC15.17 (VDD_CORE), IC15.18 (VDD_CORE), IC15.19 (VDD_CORE), IC15.20 (VDD_CORE), IC15.21 (VDD_CORE), IC15.22 (VDD_CORE), IC15.23 (VDD_CORE), IC15.24 (VDD_CORE), IC15.26 (VDD_CORE), IC15.27 (VDD_CORE), IC15.28 (VDD_CORE), IC15.29 (VDD_CORE), IC15.30 (VDD_CORE), IC15.31 (VDD_CORE), IC15.32 (VDD_CORE), IC15.33 (VDD_CORE), IC15.34 (VDD_CORE), IC15.35 (VDD_CORE), IC15.36 (VDD_CORE), IC15.45 (VDD_CORE), IC15.46 (VDD_CORE), IC15.47 (VDD_CORE), IC15.48 (VDD_CORE), IC15.49 (VDD_CORE), IC15.50 (VDD_CORE)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
VCORE_SITE3: C41.1, C44.1, C45.1, C46.1, C47.1, C48.1, C188.1, C189.1, C190.1, C191.1, C195.1, C196.1, C197.1, C198.1, C202.1, C203.1, C204.1, C205.1, C209.1, C210.1, C211.1, C212.1, IC17.1 (VDD_CORE), IC17.2 (VDD_CORE), IC17.3 (VDD_CORE), IC17.4 (VDD_CORE), IC17.14 (VDD_CORE), IC17.15 (VDD_CORE), IC17.16 (VDD_CORE), IC17.17 (VDD_CORE), IC17.18 (VDD_CORE), IC17.19 (VDD_CORE), IC17.20 (VDD_CORE), IC17.21 (VDD_CORE), IC17.22 (VDD_CORE), IC17.23 (VDD_CORE), IC17.24 (VDD_CORE), IC17.26 (VDD_CORE), IC17.27 (VDD_CORE), IC17.28 (VDD_CORE), IC17.29 (VDD_CORE), IC17.30 (VDD_CORE), IC17.31 (VDD_CORE), IC17.32 (VDD_CORE), IC17.33 (VDD_CORE), IC17.34 (VDD_CORE), IC17.35 (VDD_CORE), IC17.36 (VDD_CORE), IC17.45 (VDD_CORE), IC17.46 (VDD_CORE), IC17.47 (VDD_CORE), IC17.48 (VDD_CORE), IC17.49 (VDD_CORE), IC17.50 (VDD_CORE), IC17.51 (VDD_CORE), IC17.52 (VDD_CORE), IC17.53 (VDD_CORE), IC17.54 (VDD_CORE), IC17.55 (VDD_CORE), IC17.57 (VDD_CORE), IC17.58 (VDD_CORE), IC17.59 (VDD_CORE), IC17.60 (VDD_CORE), IC17.61 (VDD_CORE), IC17.62 (VDD_CORE), IC17.63 (VDD_CORE), IC17.64 (VDD_CORE), IC18.1 (VDD_CORE), IC18.2 (VDD_CORE), IC18.3 (VDD_CORE), IC18.4 (VDD_CORE), IC18.14 (VDD_CORE), IC18.15 (VDD_CORE), IC18.16 (VDD_CORE), IC18.17 (VDD_CORE), IC18.18 (VDD_CORE), IC18.19 (VDD_CORE), IC18.20 (VDD_CORE), IC18.21 (VDD_CORE), IC18.22 (VDD_CORE), IC18.23 (VDD_CORE), IC18.24 (VDD_CORE), IC18.26 (VDD_CORE), IC18.27 (VDD_CORE), IC18.28 (VDD_CORE), IC18.29 (VDD_CORE), IC18.30 (VDD_CORE), IC18.31 (VDD_CORE), IC18.32 (VDD_CORE), IC18.33 (VDD_CORE), IC18.34 (VDD_CORE), IC18.35 (VDD_CORE), IC18.36 (VDD_CORE), IC18.45 (VDD_CORE), IC18.46 (VDD_CORE), IC18.47 (VDD_CORE), IC18.48 (VDD_CORE), IC18.49 (VDD_CORE), IC18.50 (VDD_CORE), IC18.51 (VDD_CORE), IC18.52 (VDD_CORE), IC18.53 (VDD_CORE), IC18.54 (VDD_CORE), IC18.55 (VDD_CORE), IC18.57 (VDD_CORE), IC18.58 (VDD_CORE), IC18.59 (VDD_CORE), IC18.60 (VDD_CORE), IC18.61 (VDD_CORE), IC18.62 (VDD_CORE), IC18.63 (VDD_CORE), IC18.64 (VDD_CORE), IC19.1 (VDD_CORE), IC19.2 (VDD_CORE), IC19.3 (VDD_CORE), IC19.4 (VDD_CORE), IC19.14 (VDD_CORE), IC19.15 (VDD_CORE), IC19.16 (VDD_CORE), IC19.17 (VDD_CORE), IC19.18 (VDD_CORE), IC19.19 (VDD_CORE), IC19.20 (VDD_CORE), IC19.21 (VDD_CORE), IC19.22 (VDD_CORE), IC19.23 (VDD_CORE), IC19.24 (VDD_CORE), IC19.26 (VDD_CORE), IC19.27 (VDD_CORE), IC19.28 (VDD_CORE), IC19.29 (VDD_CORE), IC19.30 (VDD_CORE), IC19.31 (VDD_CORE), IC19.32 (VDD_CORE), IC19.33 (VDD_CORE), IC19.34 (VDD_CORE), IC19.35 (VDD_CORE), IC19.36 (VDD_CORE), IC19.45 (VDD_CORE), IC19.46 (VDD_CORE), IC19.47 (VDD_CORE), IC19.48 (VDD_CORE), IC19.49 (VDD_CORE), IC19.50 (VDD_CORE)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
VCORE_SITE4: C57.1, C60.1, C61.1, C62.1, C63.1, C64.1, C216.1, C217.1, C218.1, C219.1, C223.1, C224.1, C225.1, C226.1, C230.1, C231.1, C232.1, C233.1, C237.1, C238.1, C239.1, C240.1, IC21.1 (VDD_CORE), IC21.2 (VDD_CORE), IC21.3 (VDD_CORE), IC21.4 (VDD_CORE), IC21.14 (VDD_CORE), IC21.15 (VDD_CORE), IC21.16 (VDD_CORE), IC21.17 (VDD_CORE), IC21.18 (VDD_CORE), IC21.19 (VDD_CORE), IC21.20 (VDD_CORE), IC21.21 (VDD_CORE), IC21.22 (VDD_CORE), IC21.23 (VDD_CORE), IC21.24 (VDD_CORE), IC21.26 (VDD_CORE), IC21.27 (VDD_CORE), IC21.28 (VDD_CORE), IC21.29 (VDD_CORE), IC21.30 (VDD_CORE), IC21.31 (VDD_CORE), IC21.32 (VDD_CORE), IC21.33 (VDD_CORE), IC21.34 (VDD_CORE), IC21.35 (VDD_CORE), IC21.36 (VDD_CORE), IC21.45 (VDD_CORE), IC21.46 (VDD_CORE), IC21.47 (VDD_CORE), IC21.48 (VDD_CORE), IC21.49 (VDD_CORE), IC21.50 (VDD_CORE), IC21.51 (VDD_CORE), IC21.52 (VDD_CORE), IC21.53 (VDD_CORE), IC21.54 (VDD_CORE), IC21.55 (VDD_CORE), IC21.57 (VDD_CORE), IC21.58 (VDD_CORE), IC21.59 (VDD_CORE), IC21.60 (VDD_CORE), IC21.61 (VDD_CORE), IC21.62 (VDD_CORE), IC21.63 (VDD_CORE), IC21.64 (VDD_CORE), IC22.1 (VDD_CORE), IC22.2 (VDD_CORE), IC22.3 (VDD_CORE), IC22.4 (VDD_CORE), IC22.14 (VDD_CORE), IC22.15 (VDD_CORE), IC22.16 (VDD_CORE), IC22.17 (VDD_CORE), IC22.18 (VDD_CORE), IC22.19 (VDD_CORE), IC22.20 (VDD_CORE), IC22.21 (VDD_CORE), IC22.22 (VDD_CORE), IC22.23 (VDD_CORE), IC22.24 (VDD_CORE), IC22.26 (VDD_CORE), IC22.27 (VDD_CORE), IC22.28 (VDD_CORE), IC22.29 (VDD_CORE), IC22.30 (VDD_CORE), IC22.31 (VDD_CORE), IC22.32 (VDD_CORE), IC22.33 (VDD_CORE), IC22.34 (VDD_CORE), IC22.35 (VDD_CORE), IC22.36 (VDD_CORE), IC22.45 (VDD_CORE), IC22.46 (VDD_CORE), IC22.47 (VDD_CORE), IC22.48 (VDD_CORE), IC22.49 (VDD_CORE), IC22.50 (VDD_CORE), IC22.51 (VDD_CORE), IC22.52 (VDD_CORE), IC22.53 (VDD_CORE), IC22.54 (VDD_CORE), IC22.55 (VDD_CORE), IC22.57 (VDD_CORE), IC22.58 (VDD_CORE), IC22.59 (VDD_CORE), IC22.60 (VDD_CORE), IC22.61 (VDD_CORE), IC22.62 (VDD_CORE), IC22.63 (VDD_CORE), IC22.64 (VDD_CORE), IC23.1 (VDD_CORE), IC23.2 (VDD_CORE), IC23.3 (VDD_CORE), IC23.4 (VDD_CORE), IC23.14 (VDD_CORE), IC23.15 (VDD_CORE), IC23.16 (VDD_CORE), IC23.17 (VDD_CORE), IC23.18 (VDD_CORE), IC23.19 (VDD_CORE), IC23.20 (VDD_CORE), IC23.21 (VDD_CORE), IC23.22 (VDD_CORE), IC23.23 (VDD_CORE), IC23.24 (VDD_CORE), IC23.26 (VDD_CORE), IC23.27 (VDD_CORE), IC23.28 (VDD_CORE), IC23.29 (VDD_CORE), IC23.30 (VDD_CORE), IC23.31 (VDD_CORE), IC23.32 (VDD_CORE), IC23.33 (VDD_CORE), IC23.34 (VDD_CORE), IC23.35 (VDD_CORE), IC23.36 (VDD_CORE), IC23.45 (VDD_CORE), IC23.46 (VDD_CORE), IC23.47 (VDD_CORE), IC23.48 (VDD_CORE), IC23.49 (VDD_CORE), IC23.50 (VDD_CORE)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
VCORE_SITE5: C73.1, C76.1, C77.1, C78.1, C79.1, C80.1, C244.1, C245.1, C246.1, C247.1, C251.1, C252.1, C253.1, C254.1, C258.1, C259.1, C260.1, C261.1, C265.1, C266.1, C267.1, C268.1, IC25.1 (VDD_CORE), IC25.2 (VDD_CORE), IC25.3 (VDD_CORE), IC25.4 (VDD_CORE), IC25.14 (VDD_CORE), IC25.15 (VDD_CORE), IC25.16 (VDD_CORE), IC25.17 (VDD_CORE), IC25.18 (VDD_CORE), IC25.19 (VDD_CORE), IC25.20 (VDD_CORE), IC25.21 (VDD_CORE), IC25.22 (VDD_CORE), IC25.23 (VDD_CORE), IC25.24 (VDD_CORE), IC25.26 (VDD_CORE), IC25.27 (VDD_CORE), IC25.28 (VDD_CORE), IC25.29 (VDD_CORE), IC25.30 (VDD_CORE), IC25.31 (VDD_CORE), IC25.32 (VDD_CORE), IC25.33 (VDD_CORE), IC25.34 (VDD_CORE), IC25.35 (VDD_CORE), IC25.36 (VDD_CORE), IC25.45 (VDD_CORE), IC25.46 (VDD_CORE), IC25.47 (VDD_CORE), IC25.48 (VDD_CORE), IC25.49 (VDD_CORE), IC25.50 (VDD_CORE), IC25.51 (VDD_CORE), IC25.52 (VDD_CORE), IC25.53 (VDD_CORE), IC25.54 (VDD_CORE), IC25.55 (VDD_CORE), IC25.57 (VDD_CORE), IC25.58 (VDD_CORE), IC25.59 (VDD_CORE), IC25.60 (VDD_CORE), IC25.61 (VDD_CORE), IC25.62 (VDD_CORE), IC25.63 (VDD_CORE), IC25.64 (VDD_CORE), IC26.1 (VDD_CORE), IC26.2 (VDD_CORE), IC26.3 (VDD_CORE), IC26.4 (VDD_CORE), IC26.14 (VDD_CORE), IC26.15 (VDD_CORE), IC26.16 (VDD_CORE), IC26.17 (VDD_CORE), IC26.18 (VDD_CORE), IC26.19 (VDD_CORE), IC26.20 (VDD_CORE), IC26.21 (VDD_CORE), IC26.22 (VDD_CORE), IC26.23 (VDD_CORE), IC26.24 (VDD_CORE), IC26.26 (VDD_CORE), IC26.27 (VDD_CORE), IC26.28 (VDD_CORE), IC26.29 (VDD_CORE), IC26.30 (VDD_CORE), IC26.31 (VDD_CORE), IC26.32 (VDD_CORE), IC26.33 (VDD_CORE), IC26.34 (VDD_CORE), IC26.35 (VDD_CORE), IC26.36 (VDD_CORE), IC26.45 (VDD_CORE), IC26.46 (VDD_CORE), IC26.47 (VDD_CORE), IC26.48 (VDD_CORE), IC26.49 (VDD_CORE), IC26.50 (VDD_CORE), IC26.51 (VDD_CORE), IC26.52 (VDD_CORE), IC26.53 (VDD_CORE), IC26.54 (VDD_CORE), IC26.55 (VDD_CORE), IC26.57 (VDD_CORE), IC26.58 (VDD_CORE), IC26.59 (VDD_CORE), IC26.60 (VDD_CORE), IC26.61 (VDD_CORE), IC26.62 (VDD_CORE), IC26.63 (VDD_CORE), IC26.64 (VDD_CORE), IC27.1 (VDD_CORE), IC27.2 (VDD_CORE), IC27.3 (VDD_CORE), IC27.4 (VDD_CORE), IC27.14 (VDD_CORE), IC27.15 (VDD_CORE), IC27.16 (VDD_CORE), IC27.17 (VDD_CORE), IC27.18 (VDD_CORE), IC27.19 (VDD_CORE), IC27.20 (VDD_CORE), IC27.21 (VDD_CORE), IC27.22 (VDD_CORE), IC27.23 (VDD_CORE), IC27.24 (VDD_CORE), IC27.26 (VDD_CORE), IC27.27 (VDD_CORE), IC27.28 (VDD_CORE), IC27.29 (VDD_CORE), IC27.30 (VDD_CORE), IC27.31 (VDD_CORE), IC27.32 (VDD_CORE), IC27.33 (VDD_CORE), IC27.34 (VDD_CORE), IC27.35 (VDD_CORE), IC27.36 (VDD_CORE), IC27.45 (VDD_CORE), IC27.46 (VDD_CORE), IC27.47 (VDD_CORE), IC27.48 (VDD_CORE), IC27.49 (VDD_CORE), IC27.50 (VDD_CORE)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
VCORE_SITE6: C89.1, C92.1, C93.1, C94.1, C95.1, C96.1, C272.1, C273.1, C274.1, C275.1, C279.1, C280.1, C281.1, C282.1, C286.1, C287.1, C288.1, C289.1, C293.1, C294.1, C295.1, C296.1, IC29.1 (VDD_CORE), IC29.2 (VDD_CORE), IC29.3 (VDD_CORE), IC29.4 (VDD_CORE), IC29.14 (VDD_CORE), IC29.15 (VDD_CORE), IC29.16 (VDD_CORE), IC29.17 (VDD_CORE), IC29.18 (VDD_CORE), IC29.19 (VDD_CORE), IC29.20 (VDD_CORE), IC29.21 (VDD_CORE), IC29.22 (VDD_CORE), IC29.23 (VDD_CORE), IC29.24 (VDD_CORE), IC29.26 (VDD_CORE), IC29.27 (VDD_CORE), IC29.28 (VDD_CORE), IC29.29 (VDD_CORE), IC29.30 (VDD_CORE), IC29.31 (VDD_CORE), IC29.32 (VDD_CORE), IC29.33 (VDD_CORE), IC29.34 (VDD_CORE), IC29.35 (VDD_CORE), IC29.36 (VDD_CORE), IC29.45 (VDD_CORE), IC29.46 (VDD_CORE), IC29.47 (VDD_CORE), IC29.48 (VDD_CORE), IC29.49 (VDD_CORE), IC29.50 (VDD_CORE), IC29.51 (VDD_CORE), IC29.52 (VDD_CORE), IC29.53 (VDD_CORE), IC29.54 (VDD_CORE), IC29.55 (VDD_CORE), IC29.57 (VDD_CORE), IC29.58 (VDD_CORE), IC29.59 (VDD_CORE), IC29.60 (VDD_CORE), IC29.61 (VDD_CORE), IC29.62 (VDD_CORE), IC29.63 (VDD_CORE), IC29.64 (VDD_CORE), IC30.1 (VDD_CORE), IC30.2 (VDD_CORE), IC30.3 (VDD_CORE), IC30.4 (VDD_CORE), IC30.14 (VDD_CORE), IC30.15 (VDD_CORE), IC30.16 (VDD_CORE), IC30.17 (VDD_CORE), IC30.18 (VDD_CORE), IC30.19 (VDD_CORE), IC30.20 (VDD_CORE), IC30.21 (VDD_CORE), IC30.22 (VDD_CORE), IC30.23 (VDD_CORE), IC30.24 (VDD_CORE), IC30.26 (VDD_CORE), IC30.27 (VDD_CORE), IC30.28 (VDD_CORE), IC30.29 (VDD_CORE), IC30.30 (VDD_CORE), IC30.31 (VDD_CORE), IC30.32 (VDD_CORE), IC30.33 (VDD_CORE), IC30.34 (VDD_CORE), IC30.35 (VDD_CORE), IC30.36 (VDD_CORE), IC30.45 (VDD_CORE), IC30.46 (VDD_CORE), IC30.47 (VDD_CORE), IC30.48 (VDD_CORE), IC30.49 (VDD_CORE), IC30.50 (VDD_CORE), IC30.51 (VDD_CORE), IC30.52 (VDD_CORE), IC30.53 (VDD_CORE), IC30.54 (VDD_CORE), IC30.55 (VDD_CORE), IC30.57 (VDD_CORE), IC30.58 (VDD_CORE), IC30.59 (VDD_CORE), IC30.60 (VDD_CORE), IC30.61 (VDD_CORE), IC30.62 (VDD_CORE), IC30.63 (VDD_CORE), IC30.64 (VDD_CORE), IC31.1 (VDD_CORE), IC31.2 (VDD_CORE), IC31.3 (VDD_CORE), IC31.4 (VDD_CORE), IC31.14 (VDD_CORE), IC31.15 (VDD_CORE), IC31.16 (VDD_CORE), IC31.17 (VDD_CORE), IC31.18 (VDD_CORE), IC31.19 (VDD_CORE), IC31.20 (VDD_CORE), IC31.21 (VDD_CORE), IC31.22 (VDD_CORE), IC31.23 (VDD_CORE), IC31.24 (VDD_CORE), IC31.26 (VDD_CORE), IC31.27 (VDD_CORE), IC31.28 (VDD_CORE), IC31.29 (VDD_CORE), IC31.30 (VDD_CORE), IC31.31 (VDD_CORE), IC31.32 (VDD_CORE), IC31.33 (VDD_CORE), IC31.34 (VDD_CORE), IC31.35 (VDD_CORE), IC31.36 (VDD_CORE), IC31.45 (VDD_CORE), IC31.46 (VDD_CORE), IC31.47 (VDD_CORE), IC31.48 (VDD_CORE), IC31.49 (VDD_CORE), IC31.50 (VDD_CORE)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
VCORE_SITE7: C105.1, C108.1, C109.1, C110.1, C111.1, C112.1, C300.1, C301.1, C302.1, C303.1, C307.1, C308.1, C309.1, C310.1, C314.1, C315.1, C316.1, C317.1, C321.1, C322.1, C323.1, C324.1, IC33.1 (VDD_CORE), IC33.2 (VDD_CORE), IC33.3 (VDD_CORE), IC33.4 (VDD_CORE), IC33.14 (VDD_CORE), IC33.15 (VDD_CORE), IC33.16 (VDD_CORE), IC33.17 (VDD_CORE), IC33.18 (VDD_CORE), IC33.19 (VDD_CORE), IC33.20 (VDD_CORE), IC33.21 (VDD_CORE), IC33.22 (VDD_CORE), IC33.23 (VDD_CORE), IC33.24 (VDD_CORE), IC33.26 (VDD_CORE), IC33.27 (VDD_CORE), IC33.28 (VDD_CORE), IC33.29 (VDD_CORE), IC33.30 (VDD_CORE), IC33.31 (VDD_CORE), IC33.32 (VDD_CORE), IC33.33 (VDD_CORE), IC33.34 (VDD_CORE), IC33.35 (VDD_CORE), IC33.36 (VDD_CORE), IC33.45 (VDD_CORE), IC33.46 (VDD_CORE), IC33.47 (VDD_CORE), IC33.48 (VDD_CORE), IC33.49 (VDD_CORE), IC33.50 (VDD_CORE), IC33.51 (VDD_CORE), IC33.52 (VDD_CORE), IC33.53 (VDD_CORE), IC33.54 (VDD_CORE), IC33.55 (VDD_CORE), IC33.57 (VDD_CORE), IC33.58 (VDD_CORE), IC33.59 (VDD_CORE), IC33.60 (VDD_CORE), IC33.61 (VDD_CORE), IC33.62 (VDD_CORE), IC33.63 (VDD_CORE), IC33.64 (VDD_CORE), IC34.1 (VDD_CORE), IC34.2 (VDD_CORE), IC34.3 (VDD_CORE), IC34.4 (VDD_CORE), IC34.14 (VDD_CORE), IC34.15 (VDD_CORE), IC34.16 (VDD_CORE), IC34.17 (VDD_CORE), IC34.18 (VDD_CORE), IC34.19 (VDD_CORE), IC34.20 (VDD_CORE), IC34.21 (VDD_CORE), IC34.22 (VDD_CORE), IC34.23 (VDD_CORE), IC34.24 (VDD_CORE), IC34.26 (VDD_CORE), IC34.27 (VDD_CORE), IC34.28 (VDD_CORE), IC34.29 (VDD_CORE), IC34.30 (VDD_CORE), IC34.31 (VDD_CORE), IC34.32 (VDD_CORE), IC34.33 (VDD_CORE), IC34.34 (VDD_CORE), IC34.35 (VDD_CORE), IC34.36 (VDD_CORE), IC34.45 (VDD_CORE), IC34.46 (VDD_CORE), IC34.47 (VDD_CORE), IC34.48 (VDD_CORE), IC34.49 (VDD_CORE), IC34.50 (VDD_CORE), IC34.51 (VDD_CORE), IC34.52 (VDD_CORE), IC34.53 (VDD_CORE), IC34.54 (VDD_CORE), IC34.55 (VDD_CORE), IC34.57 (VDD_CORE), IC34.58 (VDD_CORE), IC34.59 (VDD_CORE), IC34.60 (VDD_CORE), IC34.61 (VDD_CORE), IC34.62 (VDD_CORE), IC34.63 (VDD_CORE), IC34.64 (VDD_CORE), IC35.1 (VDD_CORE), IC35.2 (VDD_CORE), IC35.3 (VDD_CORE), IC35.4 (VDD_CORE), IC35.14 (VDD_CORE), IC35.15 (VDD_CORE), IC35.16 (VDD_CORE), IC35.17 (VDD_CORE), IC35.18 (VDD_CORE), IC35.19 (VDD_CORE), IC35.20 (VDD_CORE), IC35.21 (VDD_CORE), IC35.22 (VDD_CORE), IC35.23 (VDD_CORE), IC35.24 (VDD_CORE), IC35.26 (VDD_CORE), IC35.27 (VDD_CORE), IC35.28 (VDD_CORE), IC35.29 (VDD_CORE), IC35.30 (VDD_CORE), IC35.31 (VDD_CORE), IC35.32 (VDD_CORE), IC35.33 (VDD_CORE), IC35.34 (VDD_CORE), IC35.35 (VDD_CORE), IC35.36 (VDD_CORE), IC35.45 (VDD_CORE), IC35.46 (VDD_CORE), IC35.47 (VDD_CORE), IC35.48 (VDD_CORE), IC35.49 (VDD_CORE), IC35.50 (VDD_CORE)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
VCORE_SITE8: C121.1, C124.1, C125.1, C126.1, C127.1, C128.1, C328.1, C329.1, C330.1, C331.1, C335.1, C336.1, C337.1, C338.1, C342.1, C343.1, C344.1, C345.1, C349.1, C350.1, C351.1, C352.1, IC37.1 (VDD_CORE), IC37.2 (VDD_CORE), IC37.3 (VDD_CORE), IC37.4 (VDD_CORE), IC37.14 (VDD_CORE), IC37.15 (VDD_CORE), IC37.16 (VDD_CORE), IC37.17 (VDD_CORE), IC37.18 (VDD_CORE), IC37.19 (VDD_CORE), IC37.20 (VDD_CORE), IC37.21 (VDD_CORE), IC37.22 (VDD_CORE), IC37.23 (VDD_CORE), IC37.24 (VDD_CORE), IC37.26 (VDD_CORE), IC37.27 (VDD_CORE), IC37.28 (VDD_CORE), IC37.29 (VDD_CORE), IC37.30 (VDD_CORE), IC37.31 (VDD_CORE), IC37.32 (VDD_CORE), IC37.33 (VDD_CORE), IC37.34 (VDD_CORE), IC37.35 (VDD_CORE), IC37.36 (VDD_CORE), IC37.45 (VDD_CORE), IC37.46 (VDD_CORE), IC37.47 (VDD_CORE), IC37.48 (VDD_CORE), IC37.49 (VDD_CORE), IC37.50 (VDD_CORE), IC37.51 (VDD_CORE), IC37.52 (VDD_CORE), IC37.53 (VDD_CORE), IC37.54 (VDD_CORE), IC37.55 (VDD_CORE), IC37.57 (VDD_CORE), IC37.58 (VDD_CORE), IC37.59 (VDD_CORE), IC37.60 (VDD_CORE), IC37.61 (VDD_CORE), IC37.62 (VDD_CORE), IC37.63 (VDD_CORE), IC37.64 (VDD_CORE), IC38.1 (VDD_CORE), IC38.2 (VDD_CORE), IC38.3 (VDD_CORE), IC38.4 (VDD_CORE), IC38.14 (VDD_CORE), IC38.15 (VDD_CORE), IC38.16 (VDD_CORE), IC38.17 (VDD_CORE), IC38.18 (VDD_CORE), IC38.19 (VDD_CORE), IC38.20 (VDD_CORE), IC38.21 (VDD_CORE), IC38.22 (VDD_CORE), IC38.23 (VDD_CORE), IC38.24 (VDD_CORE), IC38.26 (VDD_CORE), IC38.27 (VDD_CORE), IC38.28 (VDD_CORE), IC38.29 (VDD_CORE), IC38.30 (VDD_CORE), IC38.31 (VDD_CORE), IC38.32 (VDD_CORE), IC38.33 (VDD_CORE), IC38.34 (VDD_CORE), IC38.35 (VDD_CORE), IC38.36 (VDD_CORE), IC38.45 (VDD_CORE), IC38.46 (VDD_CORE), IC38.47 (VDD_CORE), IC38.48 (VDD_CORE), IC38.49 (VDD_CORE), IC38.50 (VDD_CORE), IC38.51 (VDD_CORE), IC38.52 (VDD_CORE), IC38.53 (VDD_CORE), IC38.54 (VDD_CORE), IC38.55 (VDD_CORE), IC38.57 (VDD_CORE), IC38.58 (VDD_CORE), IC38.59 (VDD_CORE), IC38.60 (VDD_CORE), IC38.61 (VDD_CORE), IC38.62 (VDD_CORE), IC38.63 (VDD_CORE), IC38.64 (VDD_CORE), IC39.1 (VDD_CORE), IC39.2 (VDD_CORE), IC39.3 (VDD_CORE), IC39.4 (VDD_CORE), IC39.14 (VDD_CORE), IC39.15 (VDD_CORE), IC39.16 (VDD_CORE), IC39.17 (VDD_CORE), IC39.18 (VDD_CORE), IC39.19 (VDD_CORE), IC39.20 (VDD_CORE), IC39.21 (VDD_CORE), IC39.22 (VDD_CORE), IC39.23 (VDD_CORE), IC39.24 (VDD_CORE), IC39.26 (VDD_CORE), IC39.27 (VDD_CORE), IC39.28 (VDD_CORE), IC39.29 (VDD_CORE), IC39.30 (VDD_CORE), IC39.31 (VDD_CORE), IC39.32 (VDD_CORE), IC39.33 (VDD_CORE), IC39.34 (VDD_CORE), IC39.35 (VDD_CORE), IC39.36 (VDD_CORE), IC39.45 (VDD_CORE), IC39.46 (VDD_CORE), IC39.47 (VDD_CORE), IC39.48 (VDD_CORE), IC39.49 (VDD_CORE), IC39.50 (VDD_CORE)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
VFB_SITE1: C8.2, IC1.1 (VFB), R5.2, R6.A, R6A.1
VFB_SITE2: C24.2, IC2.1 (VFB), R13.2, R14.A, R14A.1
VFB_SITE3: C40.2, IC3.1 (VFB), R21.2, R22.A, R22A.1
VFB_SITE4: C56.2, IC4.1 (VFB), R29.2, R30.A, R30A.1
VFB_SITE5: C72.2, IC5.1 (VFB), R37.2, R38.A, R38A.1
VFB_SITE6: C88.2, IC6.1 (VFB), R45.2, R46.A, R46A.1
VFB_SITE7: C104.2, IC7.1 (VFB), R53.2, R54.A, R54A.1
VFB_SITE8: C120.2, IC8.1 (VFB), R61.2, R62.A, R62A.1

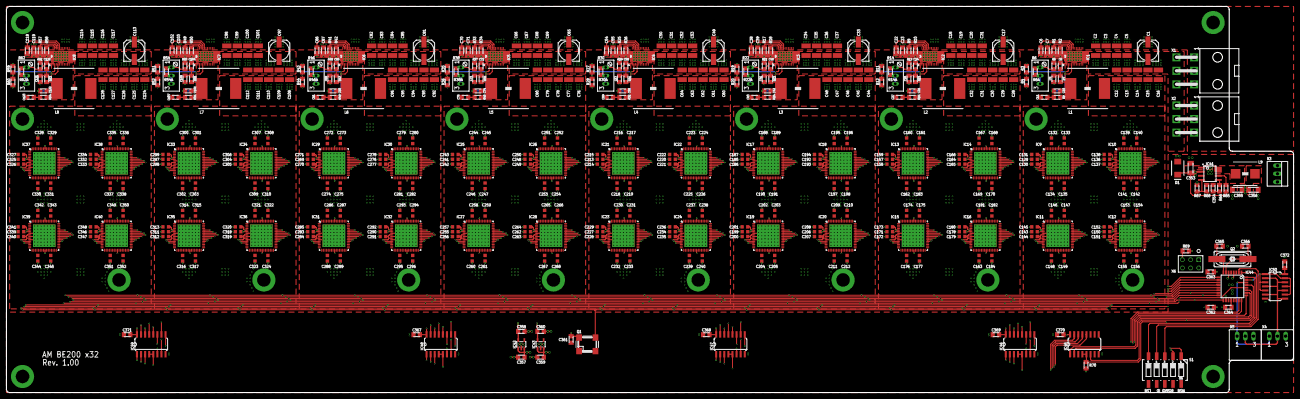
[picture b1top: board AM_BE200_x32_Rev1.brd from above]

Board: 4 copper layers, 400.0 x 120.0 mm, 519 parts (0 on the bottom side), 152 nets.

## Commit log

2014-06-05 Rev1 32 Chip Board
2014-06-06 Add BOM
2014-06-06 Remove pdf files
